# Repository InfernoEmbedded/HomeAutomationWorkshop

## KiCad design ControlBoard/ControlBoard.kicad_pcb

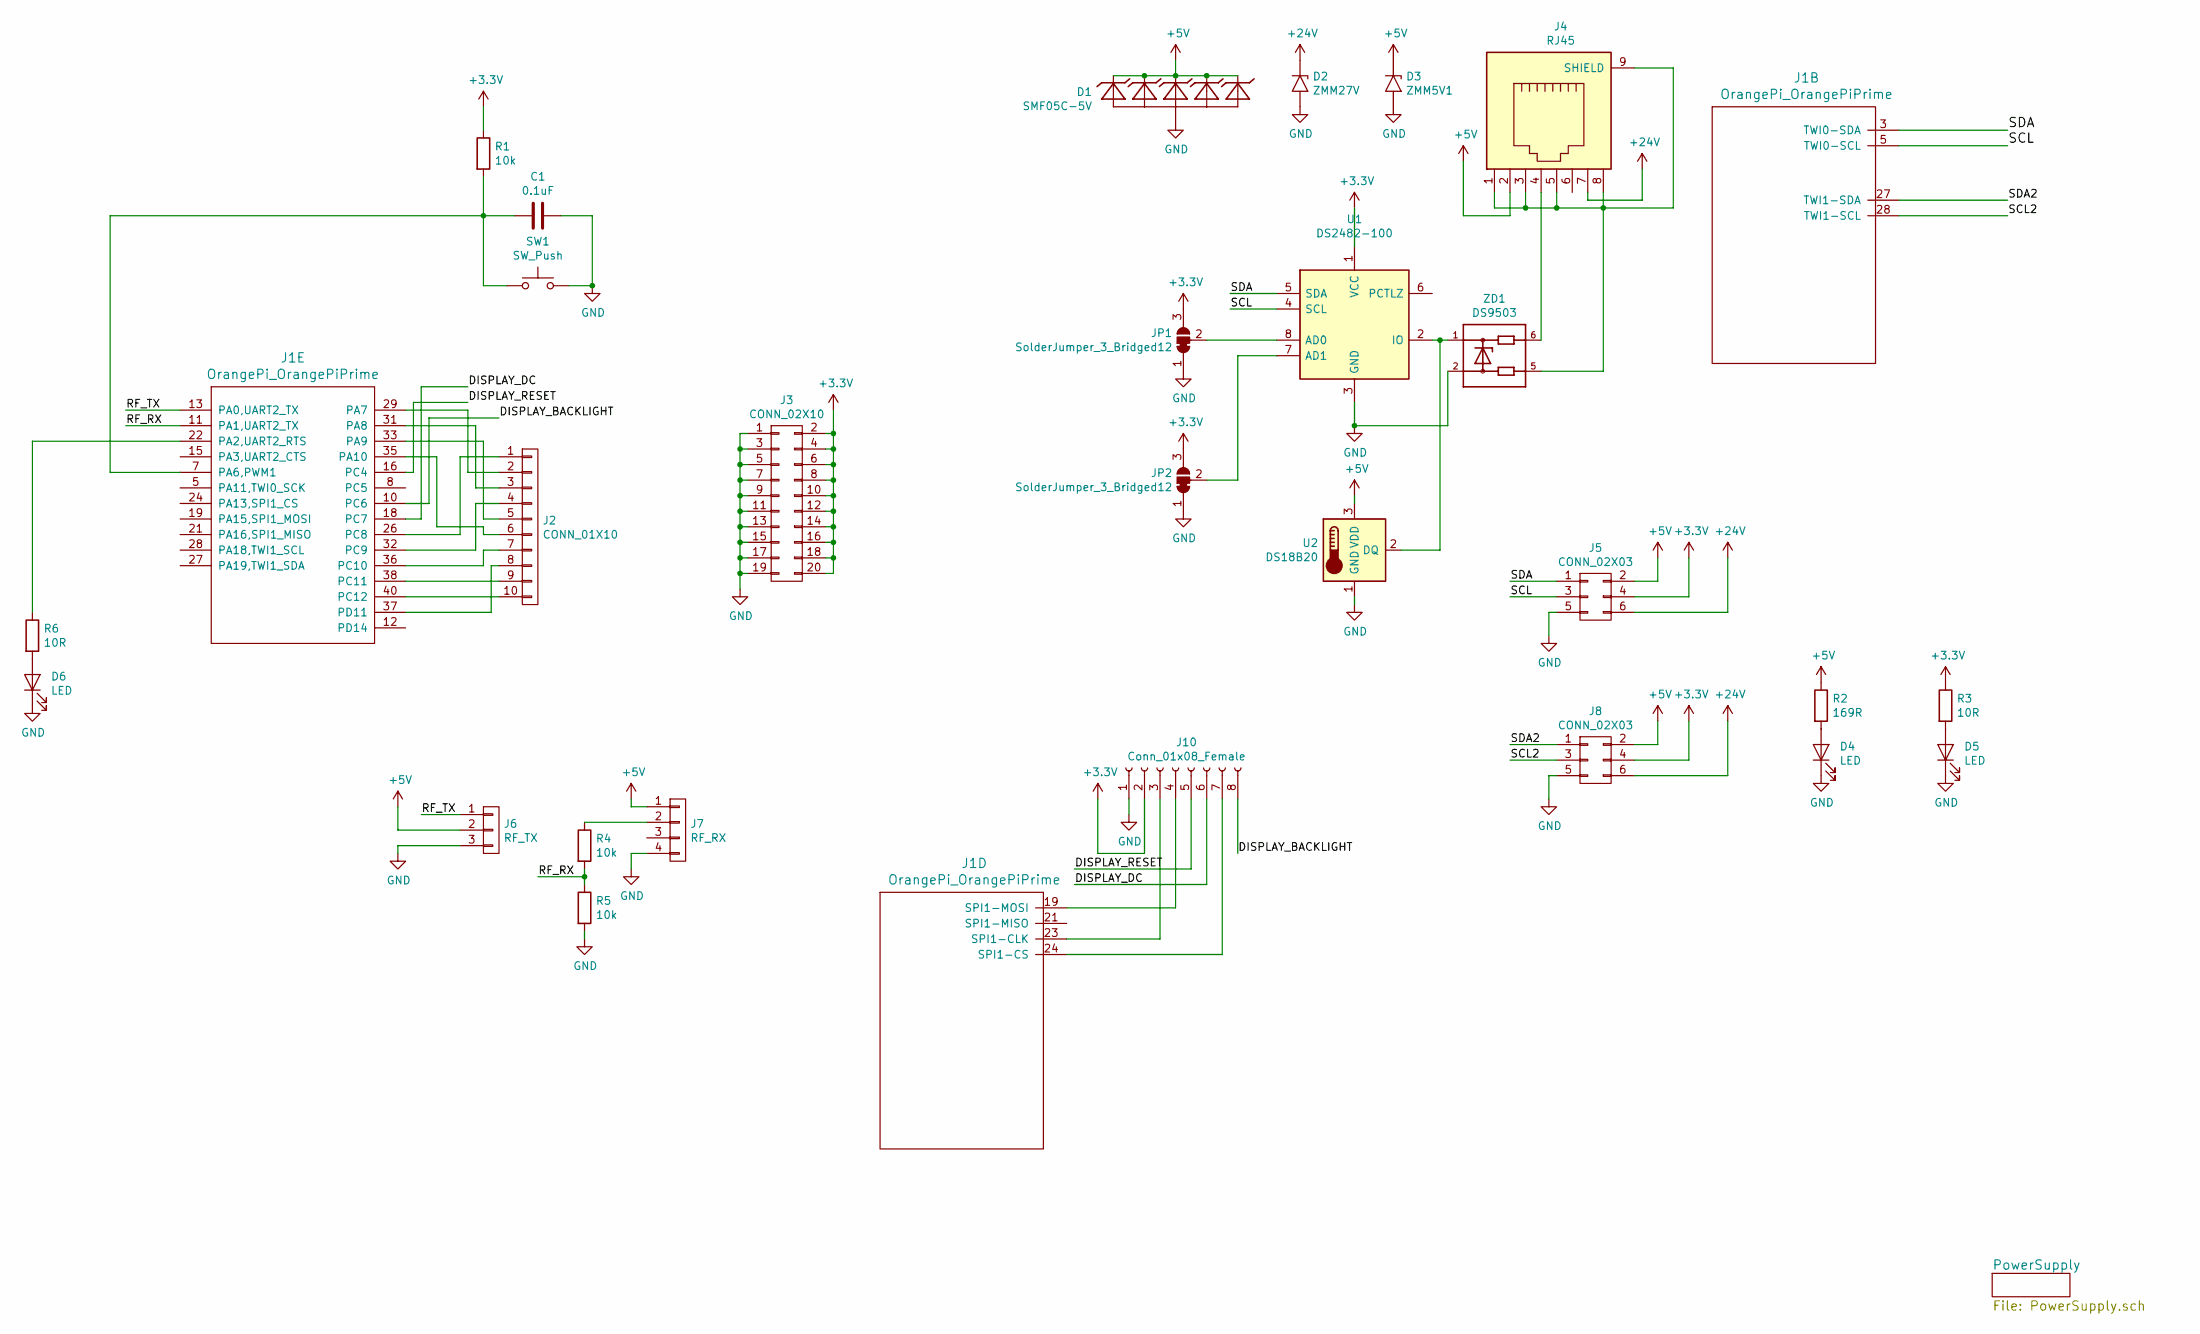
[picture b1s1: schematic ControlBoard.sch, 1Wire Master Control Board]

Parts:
C1: 0.1uF; C_0603
D1: SMF05C-5V; SC70-6
D2: ZMM27V; D_MiniMELF
D3: ZMM5V1; D_MiniMELF
D4, D5, D6: LED; LED_0603_1608Metric
J1: OrangePi_OrangePiPrime; OrangePiPrime
J2: CONN_01X10; PinHeader_1x10_P2.54mm_Vertical
J3: CONN_02X10; PinHeader_2x10_P2.54mm_Vertical
J4: RJ45; RJ45-ChinaSMD
J5, J8: CONN_02X03; PinHeader_2x03_P2.54mm_Vertical
J6: RF_TX; PinHeader_1x03_P2.54mm_Vertical
J7: RF_RX; PinHeader_1x04_P2.54mm_Vertical
J10: Conn_01x08_Female; PinSocket_1x08_P2.54mm_Vertical
JP1, JP2: SolderJumper_3_Bridged12; SolderJumper-3_P1.3mm_Bridged12_RoundedPad1.0x1.5mm
R1, R4, R5: 10k; R_0603
R2: 169R; R_0603_1608Metric
R3, R6: 10R; R_0603_1608Metric
SW1: SW_Push; SW_SPST_B3S-1000
U1: DS2482-100; SOIC-8_3.9x4.9mm_Pitch1.27mm
U2: DS18B20; TO-92_Inline_Narrow_Oval
ZD1: DS9503; TSOC6

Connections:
+3V3: J3.2, J3.4, J3.6, J3.8, J3.10, J3.12, J3.14, J3.16, J3.18, J3.20, J5.4, J8.4, J10.2, JP1.3 (B), JP2.3 (B), R1.1, R3.1, U1.1 (VCC); also elsewhere on the board
+5V: D1.1 (C1), D1.3 (C2), D1.4 (C3), D1.5 (C4), D1.6 (C5), D3.1 (A1), J4.2, J5.2, J6.2, J7.1, J8.2, R2.1, U2.3 (VDD); also elsewhere on the board
+24V: D2.1 (A1), J4.7, J5.6, J8.6; also elsewhere on the board
/DISPLAY_BACKLIGHT: J1.10 (PC6), J10.8
/DISPLAY_DC: J1.18 (PC7), J10.6
/DISPLAY_RESET: J1.16 (PC4), J10.5
/RF_RX: J1.11 (UART2-RX), R4.2, R5.1
/RF_TX: J1.13 (UART2-TX), J6.1
/SCL: J1.5 (TWI0-SCL), J5.3, U1.4 (SCL)
/SDA: J1.3 (TWI0-SDA), J5.1, U1.5 (SDA)
GND: C1.1, D1.2 (A), D2.2 (A2), D3.2 (A2), D4.1 (K), D5.1 (K), D6.1 (K), J3.1, J3.3, J3.5, J3.7, J3.9, J3.11, J3.13, J3.15, J3.17, J3.19, J5.5, J6.3, J7.4, J8.5, J10.1, JP1.1 (A), JP2.1 (A), R5.2, SW1.2, U1.3 (GND), U2.1 (GND), ZD1.2; also elsewhere on the board
unnamed: C1.2, J1.7 (PA6,PWM1), R1.2, SW1.1
unnamed: D4.2 (A), R2.2
unnamed: D5.2 (A), R3.2
unnamed: D6.2 (A), R6.2
unnamed: J1.19 (SPI1-MOSI), J10.4
unnamed: J1.22 (UART2-RTS), R6.1
unnamed: J1.23 (SPI1-CLK), J10.3
unnamed: J1.24 (SPI1-CS), J10.7
unnamed: J1.26 (PC8), J2.1
unnamed: J1.29 (PA7), J2.2
unnamed: J1.31 (PA8), J2.3
unnamed: J1.32 (PC9), J2.4
unnamed: J1.33 (PA9), J2.5
unnamed: J1.35 (PA10), J2.6
unnamed: J1.36 (PC10), J2.7
unnamed: J1.37 (PD11), J2.8
unnamed: J1.38 (PC11), J2.9
unnamed: J1.40 (PC12), J2.10
unnamed: J4.1, J4.3, J4.5, J4.8, J4.9 (SHIELD), ZD1.5
unnamed: J4.4, ZD1.6
unnamed: J7.2, R4.1
unnamed: JP1.2 (C), U1.8 (AD0)
unnamed: JP2.2 (C), U1.7 (AD1)
unnamed: U1.2 (IO), U2.2 (DQ), ZD1.1

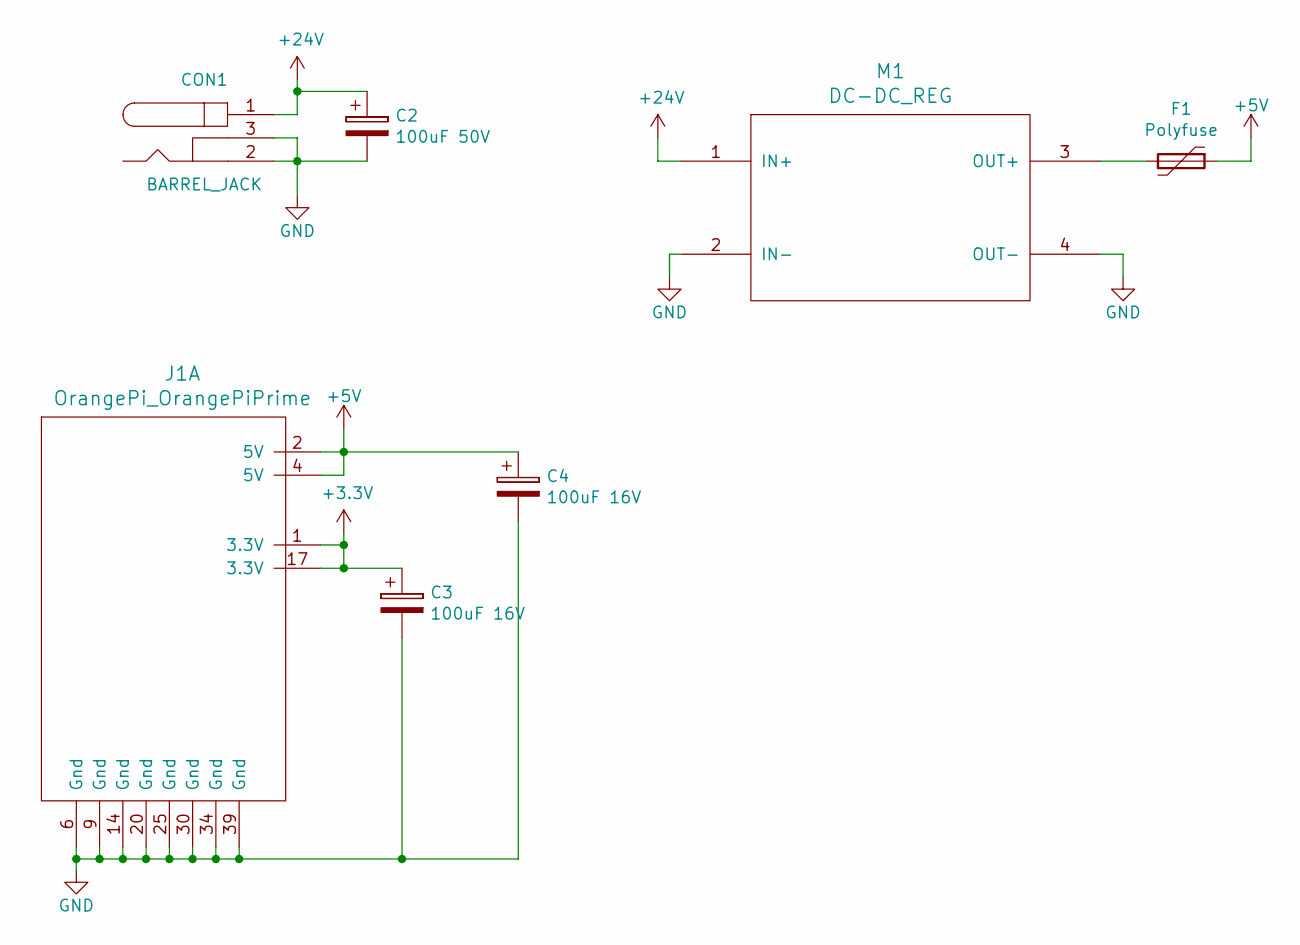
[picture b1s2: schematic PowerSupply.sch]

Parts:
C2: 100uF 50V; C_1206_3216Metric
C3, C4: 100uF 16V; C_1206_3216Metric
CON1: BARREL_JACK
F1: Polyfuse; Fuse_1206_3216Metric
J1: OrangePi_OrangePiPrime; OrangePiPrime
M1: DC-DC_REG; D-SUN_DC_DC

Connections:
+3V3: C3.1, J1.1 (3.3V), J1.17 (3.3V); also elsewhere on the board
+5V: C4.1, F1.1, J1.2 (5V), J1.4 (5V); also elsewhere on the board
+24V: C2.1, CON1.1, M1.1 (IN+); also elsewhere on the board
GND: C2.2, C3.2, C4.2, CON1.2, CON1.3, J1.6 (Gnd), J1.9 (Gnd), J1.14 (Gnd), J1.20 (Gnd), J1.25 (Gnd), J1.30 (Gnd), J1.34 (Gnd), J1.39 (Gnd), M1.2 (IN-), M1.4 (OUT-); also elsewhere on the board
unnamed: F1.2, M1.3 (OUT+)

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
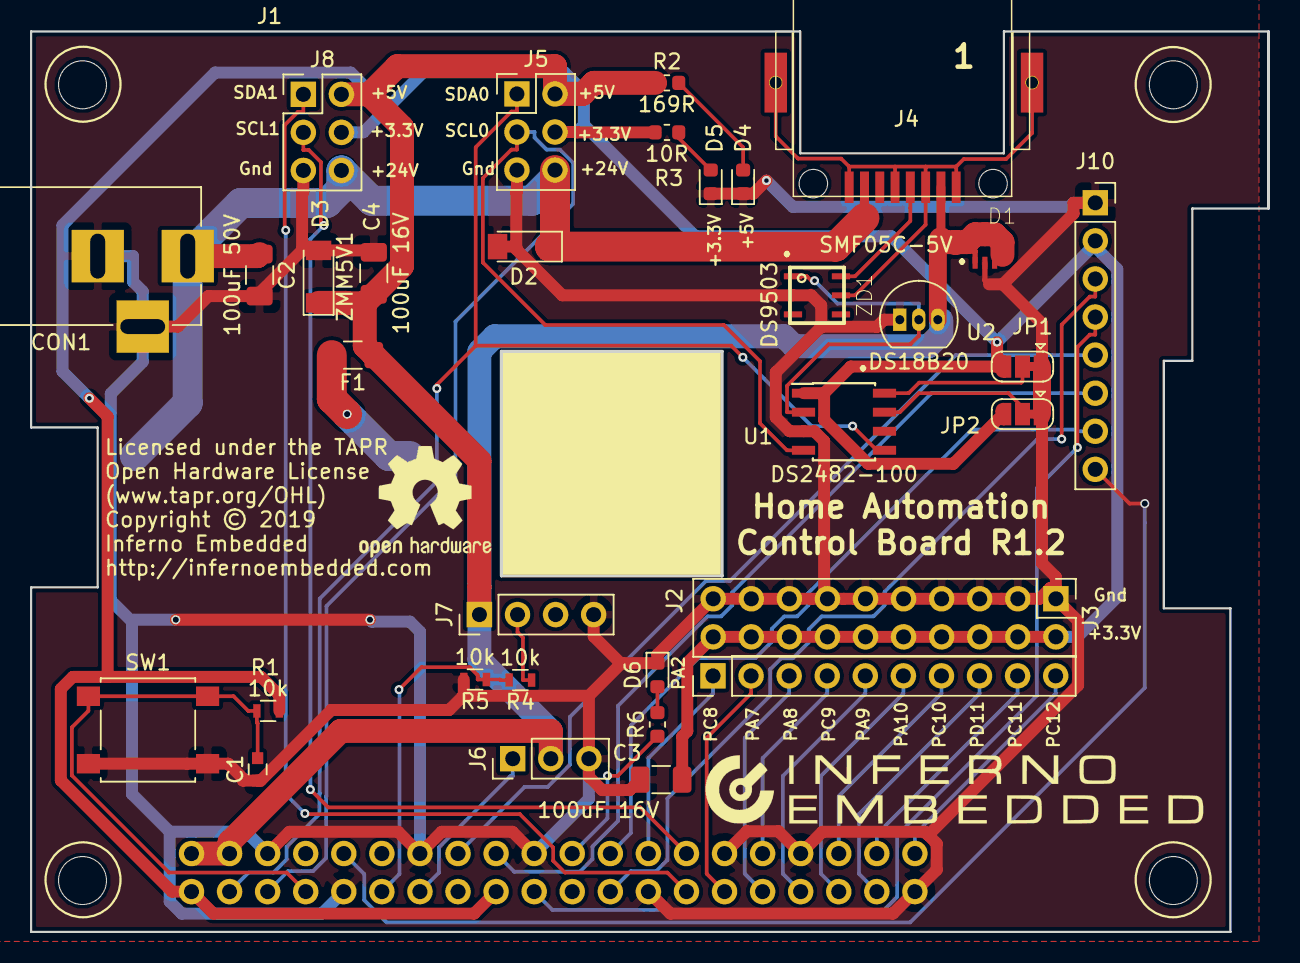
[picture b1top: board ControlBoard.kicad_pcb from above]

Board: 2 copper layers, 82.5 x 60.0 mm, 34 parts (1 on the bottom side), 36 nets.

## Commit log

2019-01-10 Pull in the 1Wire firmware repo
2019-01-10 Template for Device MAC addresses
2019-01-12 Add a simple burnin script.
    At the moment it just boots the board, logs in, and collects the
    eth0 mac address. I am sure there is more verification it could do
    than that, but this is a starting point.
2019-01-13 Add testing of ethernet jacks
2019-01-13 Test 1-Wire
2019-01-13 Tested boards
2019-01-13 Add some MAC addresses
2019-01-14 Add initial prereqs
2019-01-15 Add MACs from burnin script
2019-01-15 Automate generation of a DHCP config for the lab.
2019-01-15 Add MAC for machine 25
2019-01-16 Move Network stufii to the infrastructure dir
2019-01-16 Add Mikal's GPIO for Orange Pi patches
2019-01-16 Add the start of workshop instructions
2019-01-17 Tell MBed where to find the source to MbedOS
2019-01-17 WIP: more instructions
2019-01-17 Clarify pre-workshop docs
2019-01-17 Dry-run the prerequisites doc
    Just fixing up a couple of minor typos in the pre-work instructions. Tested on a mostly clean Ubuntu 18.10 VM.
2019-01-19 Update softdevice with the latest fixes
2019-01-19 Add Mosquitto clients to the prereqs
2019-01-19 flesh out the instructions
2019-01-23 spelling fixes and owfs gateway does not need to be installed anymore
2019-01-23 small fixes
2019-01-23 warning that sshd start is very slow
2019-01-24 Remove dhcpd.conf
2019-01-24 Add Eclipse projects
2019-01-24 Add 1Wire trademark signs
2019-01-24 Move OWFS->MQTT gateway install later
2019-01-24 Doco cleanup
2019-01-24 Add a Bill of Materials for the workshop
2019-01-24 Revision 1.2 of the Control Board - All resisitors to 10k - Add solder jumpers to set i2c address - Move the GPIO +V line to 3.3V - Move pushbutton to PA6 as it has an interrupt associated with it - 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
2019-01-27 Controlboard updates - Add second I2C port - Add Power LEDs (5V & 3.3V) - Add GPIO LED on PA2 - Add header for ST7735 LCD - Add missing mounting holes - Save OrangePiPrime footprints and symbols as e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
2019-01-30 Add a note about not pluggin ethernet into the 1wire port
2019-01-30 Add Hat assembly instructions
2019-04-08 Add more docs on the relay connection
2019-04-08 Make the GPIO header more obvious
2019-04-08 Shrink the gpio header image a bit more
2019-04-08 Relay docs again (#10)
    * Make the GPIO header more obvious

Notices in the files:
ControlBoard/ControlBoard.kicad_pcb:
Licensed under the TAPR
Open Hardware License
Copyright © 2019
